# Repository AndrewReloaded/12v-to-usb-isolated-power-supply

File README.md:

# 12v-to-usb-isolated-power-supply
 Isolated power supply for USB powered Bluetooth receiver

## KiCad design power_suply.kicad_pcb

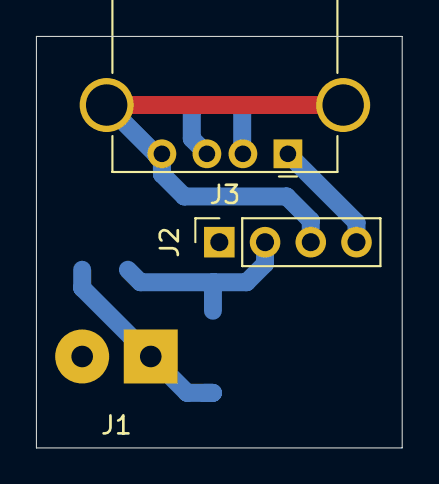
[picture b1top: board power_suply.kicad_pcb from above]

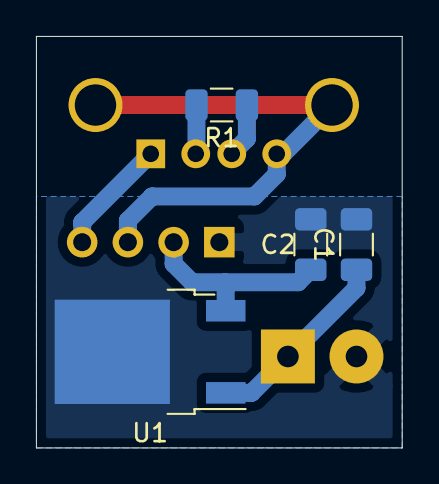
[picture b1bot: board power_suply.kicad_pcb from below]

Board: 2 copper layers, 20.3 x 22.9 mm, 7 parts (4 on the bottom side), 7 nets.

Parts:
C1: 0.33uF; C_1206_3216Metric
C2: 0.1 uF; C_1206_3216Metric
J1: PWR; SolderWirePad_1x02_P3.81mm_Drill1.2mm
J2: AM1S-1205SZ; PinSocket_1x04_P2.54mm_Vertical
J3: USB_A; USB_A_Stewart_SS-52100-001_Horizontal
R1: 10k; R_1206_3216Metric
U1: LM78M05_TO252; TO-252-2

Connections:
unnamed: C1.1, J1.1, U1.1
unnamed: C1.2, C2.2, J1.2, J2.1, U1.2
unnamed: C2.1, J2.2, U1.3
unnamed: J2.3, J3.4, J3.5
unnamed: J2.4, J3.1
unnamed: J3.2, R1.2
unnamed: J3.3, R1.1

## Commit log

2019-10-18 capasitor removed
2019-10-18 readme updated
